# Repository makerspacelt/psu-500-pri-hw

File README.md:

This is atempt to design a 500W PSU primary side 

Dev NOTE: before commit, run `./kibot.sh` to regenerate documentation, gerbers and other assets.

* [schematics.pdf](gen/schematics.pdf)
* [pcb.pdf with dimensions](gen/pcb.pdf)

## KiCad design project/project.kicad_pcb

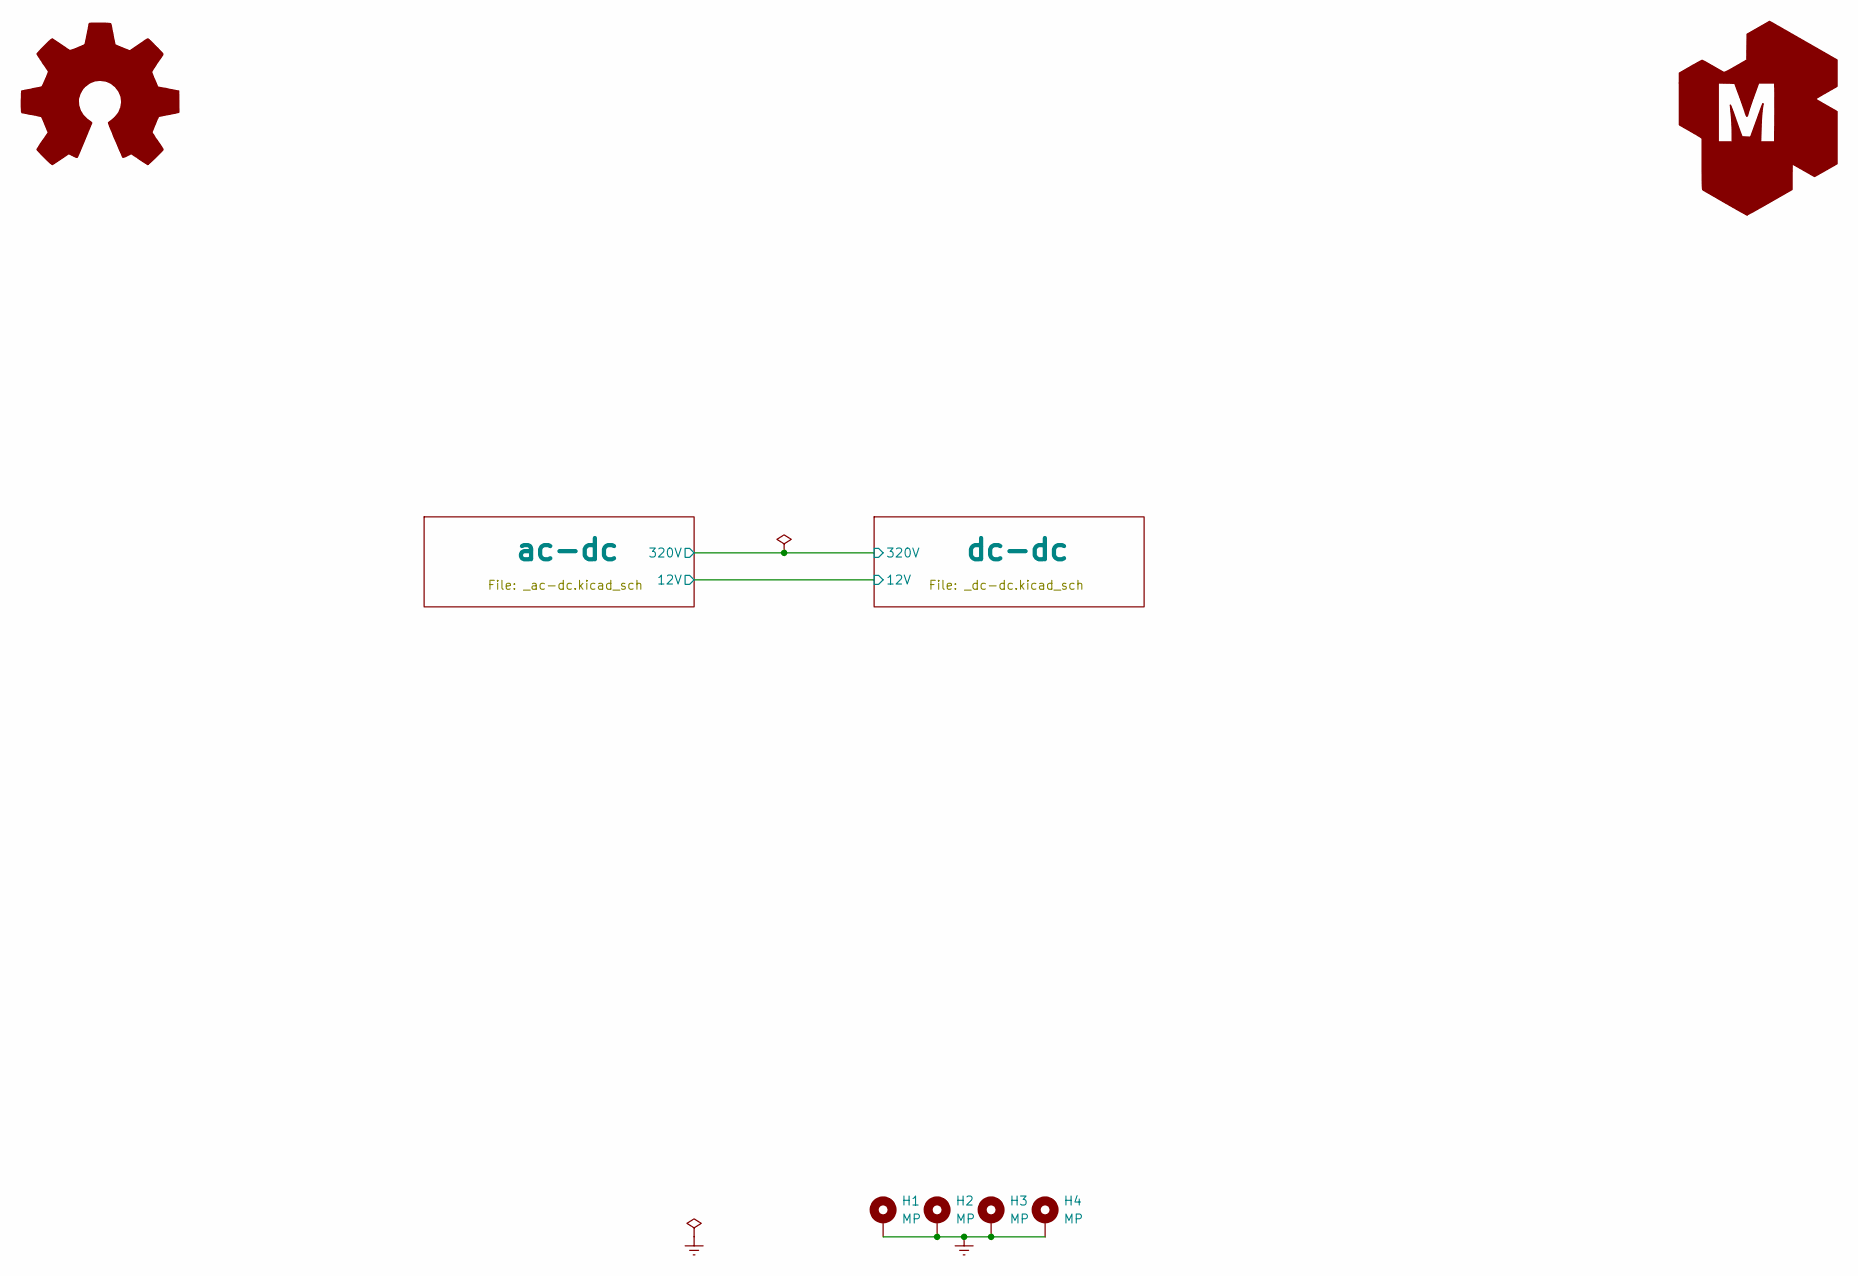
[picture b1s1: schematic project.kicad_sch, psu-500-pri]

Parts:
G1: Logo_Open_Hardware_Large; OSHW-Symbol_6.7x6mm_SilkScreen
G2: LOGO_KMS; logo_kms_small_silkscreen
H1, H2, H3, H4: MP; MountingHole_4.3mm_M4_Pad_Via

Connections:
Earth: H1.1, H2.1, H3.1, H4.1; also elsewhere on the board

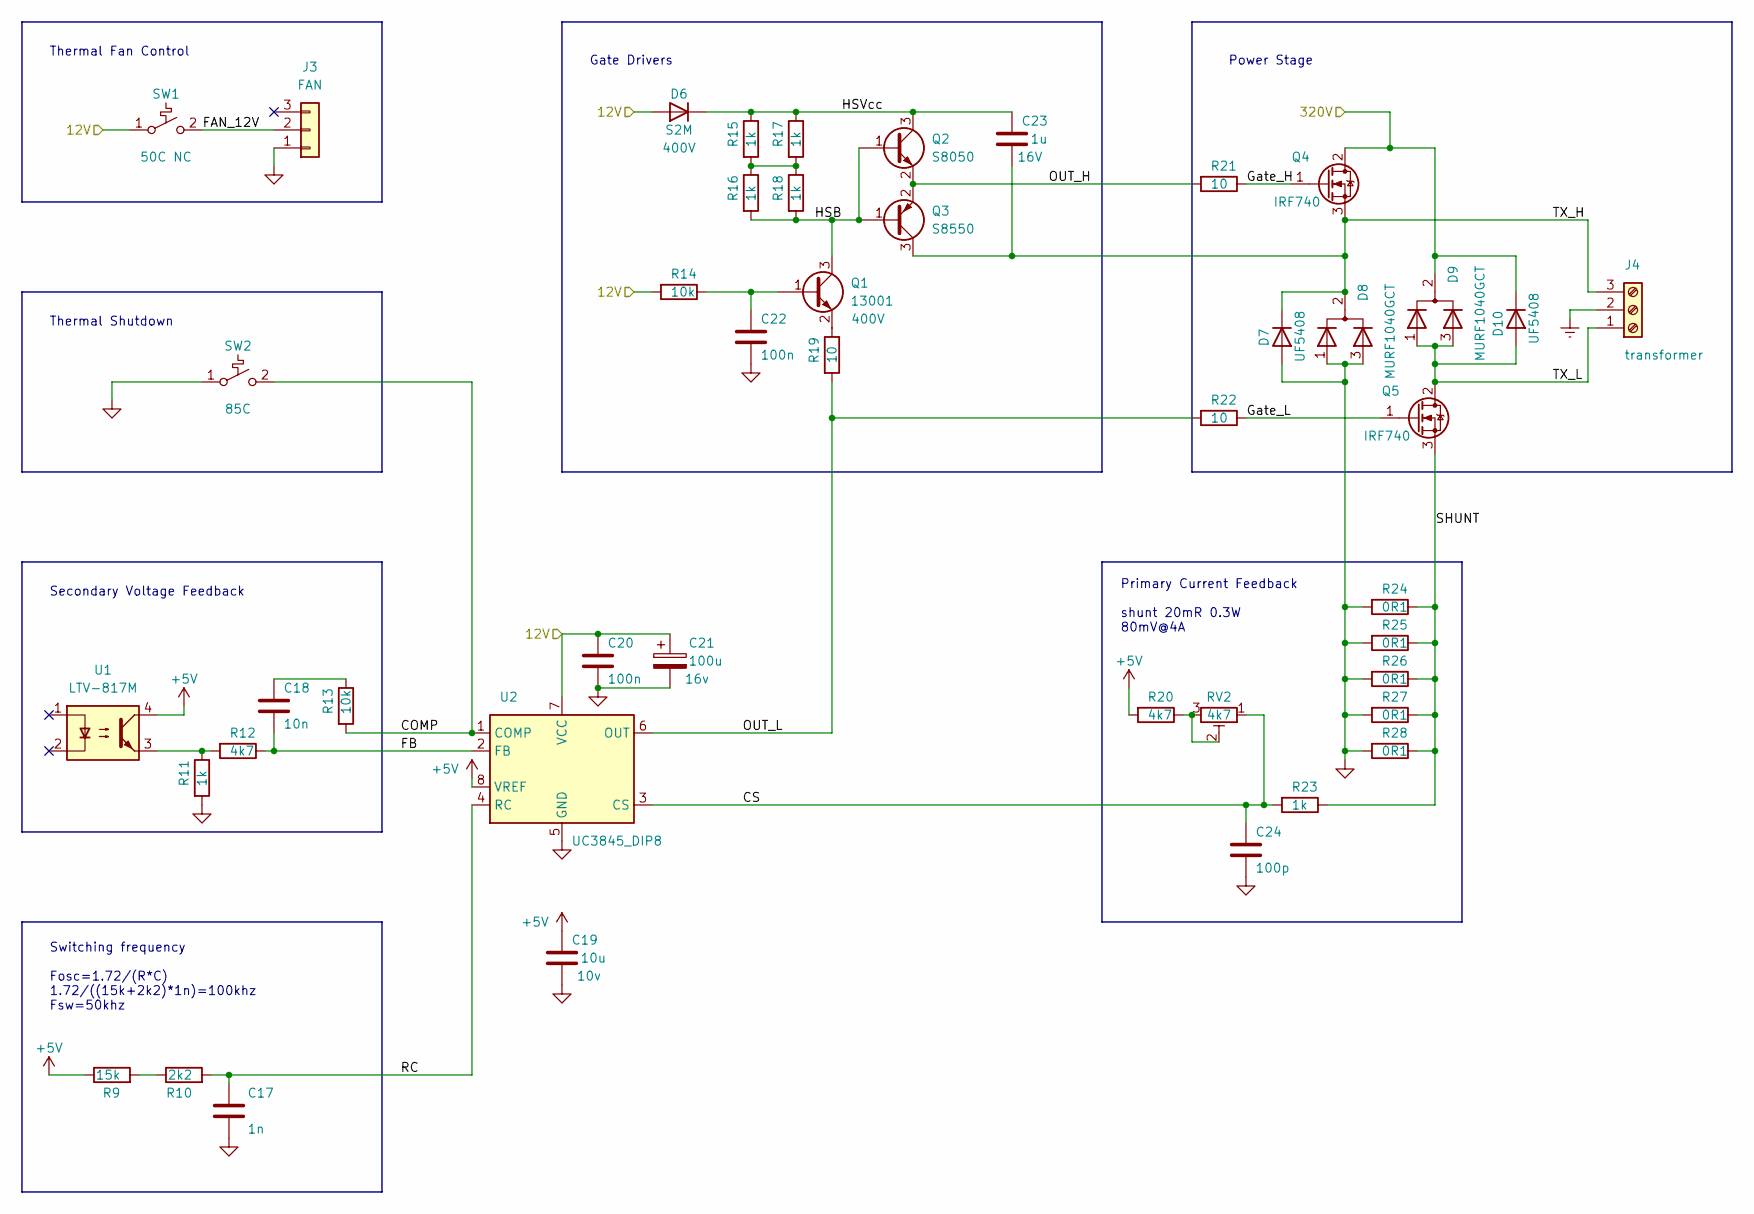
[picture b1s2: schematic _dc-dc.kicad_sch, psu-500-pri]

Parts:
C17: 1n; C_0805_2012Metric_Pad1.18x1.45mm_HandSolder
C18: 10n; C_0805_2012Metric_Pad1.18x1.45mm_HandSolder
C19: 10u; C_0805_2012Metric_Pad1.18x1.45mm_HandSolder
C20, C22: 100n; C_0805_2012Metric_Pad1.18x1.45mm_HandSolder
C21: 100u; CP_Elec_10x10
C23: 1u; C_0805_2012Metric_Pad1.18x1.45mm_HandSolder
C24: 100p; C_0805_2012Metric_Pad1.18x1.45mm_HandSolder
D6: S2M; D_SMA_Handsoldering
D7, D10: UF5408; D_DO-201AD_P15.24mm_Horizontal
D8, D9: MURF1040GCT; TO-220-3_Horizontal_TabUp; LCSC# C2995510
J3: FAN; Molex_KK-254_AE-6410-03A_1x03_P2.54mm_Vertical
J4: transformer; TerminalBlock_Phoenix_MKDS-1,5-3_1x03_P5.00mm_Horizontal
Q1: 13001; SOT-23; LCSC# C5261071
Q2: S8050; SOT-23
Q3: S8550; SOT-23
Q4, Q5: IRF740; TO-220-3_Horizontal_TabUp
R9: 15k; R_0805_2012Metric_Pad1.20x1.40mm_HandSolder
R10: 2k2; R_0805_2012Metric_Pad1.20x1.40mm_HandSolder
R11, R15, R16, R17, R18, R23: 1k; R_0805_2012Metric_Pad1.20x1.40mm_HandSolder
R12, R20: 4k7; R_0805_2012Metric_Pad1.20x1.40mm_HandSolder
R13, R14: 10k; R_0805_2012Metric_Pad1.20x1.40mm_HandSolder
R19, R21, R22: 10; R_0805_2012Metric_Pad1.20x1.40mm_HandSolder
R24, R25, R26, R27, R28: 0R1; R_0805_2012Metric_Pad1.20x1.40mm_HandSolder
RV2: 4k7; Potentiometer_Bourns_3296W_Vertical
SW1: 50C NC; TO-220-2_Horizontal_TabUp
SW2: 85C; TO-220-2_Horizontal_TabUp
U1: LTV-817M; DIP-4_W10.16mm; LCSC# C109226
U2: UC3845_DIP8; DIP-8_W7.62mm

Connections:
+5V: C19.1, R9.1, R20.2, U1.4, U2.8 (VREF)
/ac-dc/12V: C20.1, C21.1, D6.2 (A), R14.2, SW1.1 (A), U2.7 (VCC); also elsewhere on the board
/ac-dc/320V: D9.2 (A), D10.1 (K), Q4.2 (D); also elsewhere on the board
/dc-dc/COMP: R13.2, SW2.2 (B), U2.1 (COMP)
/dc-dc/CS: C24.1, R23.2, RV2.1, U2.3 (CS)
/dc-dc/FAN_12V: J3.2, SW1.2 (B)
/dc-dc/FB: C18.2, R12.1, U2.2 (FB)
/dc-dc/Gate_H: Q4.1 (G), R21.1
/dc-dc/Gate_L: Q5.1 (G), R22.1
/dc-dc/HSB: Q1.3 (C), Q2.1 (B), Q3.1 (B), R16.2, R18.2
/dc-dc/HSVcc: C23.1, D6.1 (K), Q2.3 (C), R15.1, R17.1
/dc-dc/OUT_H: Q2.2 (E), Q3.2 (E), R21.2
/dc-dc/OUT_L: R19.2, R22.2, U2.6 (OUT)
/dc-dc/RC: C17.1, R10.2, U2.4 (RC)
/dc-dc/SHUNT: Q5.3 (S), R23.1, R24.1, R25.1, R26.1, R27.1, R28.1
/dc-dc/TX_H: C23.2, D7.1 (K), D8.2 (A), J4.3, Q3.3 (C), Q4.3 (S)
/dc-dc/TX_L: D9.1 (K), D9.3 (K), D10.2 (A), J4.1, Q5.2 (D)
Earth: J4.2; also elsewhere on the board
GND: C17.2, C19.2, C20.2, C21.2, C22.2, C24.2, D7.2 (A), D8.1 (K), D8.3 (K), J3.1, R11.2, R24.2, R25.2, R26.2, R27.2, R28.2, SW2.1 (A), U2.5 (GND); also elsewhere on the board
unnamed: C18.1, R13.1
unnamed: C22.1, Q1.1 (B), R14.1
unnamed: Q1.2 (E), R19.1
unnamed: R9.2, R10.1
unnamed: R11.1, R12.2, U1.3
unnamed: R15.2, R16.1, R17.2, R18.1
unnamed: R20.1, RV2.2, RV2.3

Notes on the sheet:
Switching frequency Fosc=1.72/(R*C) 1.72/((15k+2k2)*1n)=100khz Fsw=50khz
Primary Current Feedback shunt 20mR 0.3W 80mV@4A
Gate Drivers
Thermal Fan Control
Thermal Shutdown
Secondary Voltage Feedback
Power Stage

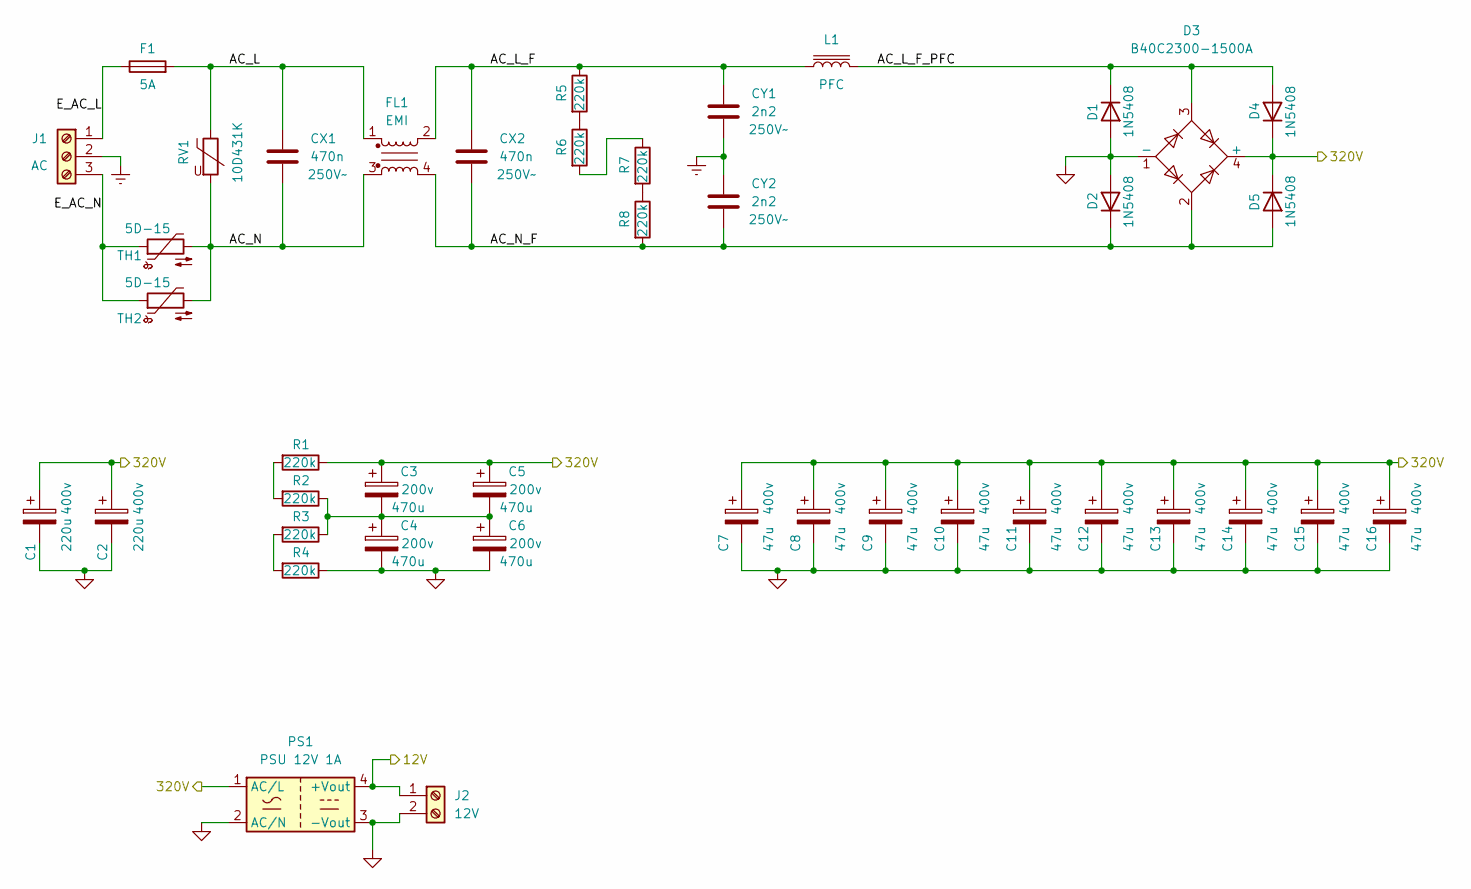
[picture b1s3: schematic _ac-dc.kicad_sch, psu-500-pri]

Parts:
C1, C2: 220u; CP_Radial_D30.0mm_P10.00mm_SnapIn
C3, C4, C5, C6: 470u; CP_Radial_D24.0mm_P10.00mm_SnapIn
C7, C8, C9, C10, C11, C12, C13, C14, C15, C16: 47u; CP_Radial_D16.0mm_P7.50mm
CX1, CX2: 470n; C_Rect_L19.0mm_W9.0mm_P15.00mm_MKS4
CY1, CY2: 2n2; C_Disc_D9.0mm_W5.0mm_P7.50mm
D1, D2, D4, D5: 1N5408; D_DO-201AD_P15.24mm_Horizontal
D3: B40C2300-1500A; Diode_Bridge_19.0x3.5x10.0mm_P5.0mm
F1: 5A; Fuseholder_Cylinder-5x20mm_Schurter_0031_8201_Horizontal_Op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
FL1: EMI; L_CommonMode_Toroid_Vertical_L34.3mm_W20.3mm_Px15.24mm_Py22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
J1: AC; TerminalBlock_Phoenix_MKDS-1,5-3_1x03_P5.00mm_Horizontal
J2: 12V; TerminalBlock_Phoenix_MKDS-1,5-2-5.08_1x02_P5.08mm_Horizont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
L1: PFC; JWT_A3963_1x02_P3.96mm_Vertical
PS1: PSU 12V 1A; Converter_ACDC_HiLink_HLK-PMxx
R1, R2, R3, R4, R5, R6, R7, R8: 220k; R_0805_2012Metric_Pad1.20x1.40mm_HandSolder
RV1: 10D431K; RV_Disc_D12mm_W5.4mm_P7.5mm; LCSC# C317794
TH1, TH2: 5D-15; C_Disc_D12.5mm_W5.0mm_P7.50mm

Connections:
/ac-dc/12V: J2.1, PS1.4 (+Vout); also elsewhere on the board
/ac-dc/320V: C1.1, C2.1, C3.1, C5.1, C7.1, C8.1, C9.1, C10.1, C11.1, C12.1, C13.1, C14.1, C15.1, C16.1, D3.4 (+), D4.1 (K), D5.1 (K), PS1.1 (AC/L), R1.1; also elsewhere on the board
/ac-dc/AC_L: CX1.1, F1.2, FL1.1, RV1.1
/ac-dc/AC_L_F: CX2.1, CY1.1, FL1.2, L1.1, R5.1
/ac-dc/AC_L_F_PFC: D1.1 (K), D3.3, D4.2 (A), L1.2
/ac-dc/AC_N: CX1.2, FL1.3, RV1.2, TH1.2, TH2.2
/ac-dc/AC_N_F: CX2.2, CY2.2, D2.1 (K), D3.2, D5.2 (A), FL1.4, R8.2
/ac-dc/E_AC_L: F1.1, J1.1
/ac-dc/E_AC_N: J1.3, TH1.1, TH2.1
Earth: CY1.2, CY2.1, J1.2; also elsewhere on the board
GND: C1.2, C2.2, C4.2, C6.2, C7.2, C8.2, C9.2, C10.2, C11.2, C12.2, C13.2, C14.2, C15.2, C16.2, D1.2 (A), D2.2 (A), D3.1 (-), J2.2, PS1.2 (AC/N), PS1.3 (-Vout), R4.1; also elsewhere on the board
unnamed: C3.2, C4.1, C5.2, C6.1, R2.1, R3.1
unnamed: R1.2, R2.2
unnamed: R3.2, R4.2
unnamed: R5.2, R6.1
unnamed: R6.2, R7.1
unnamed: R7.2, R8.1

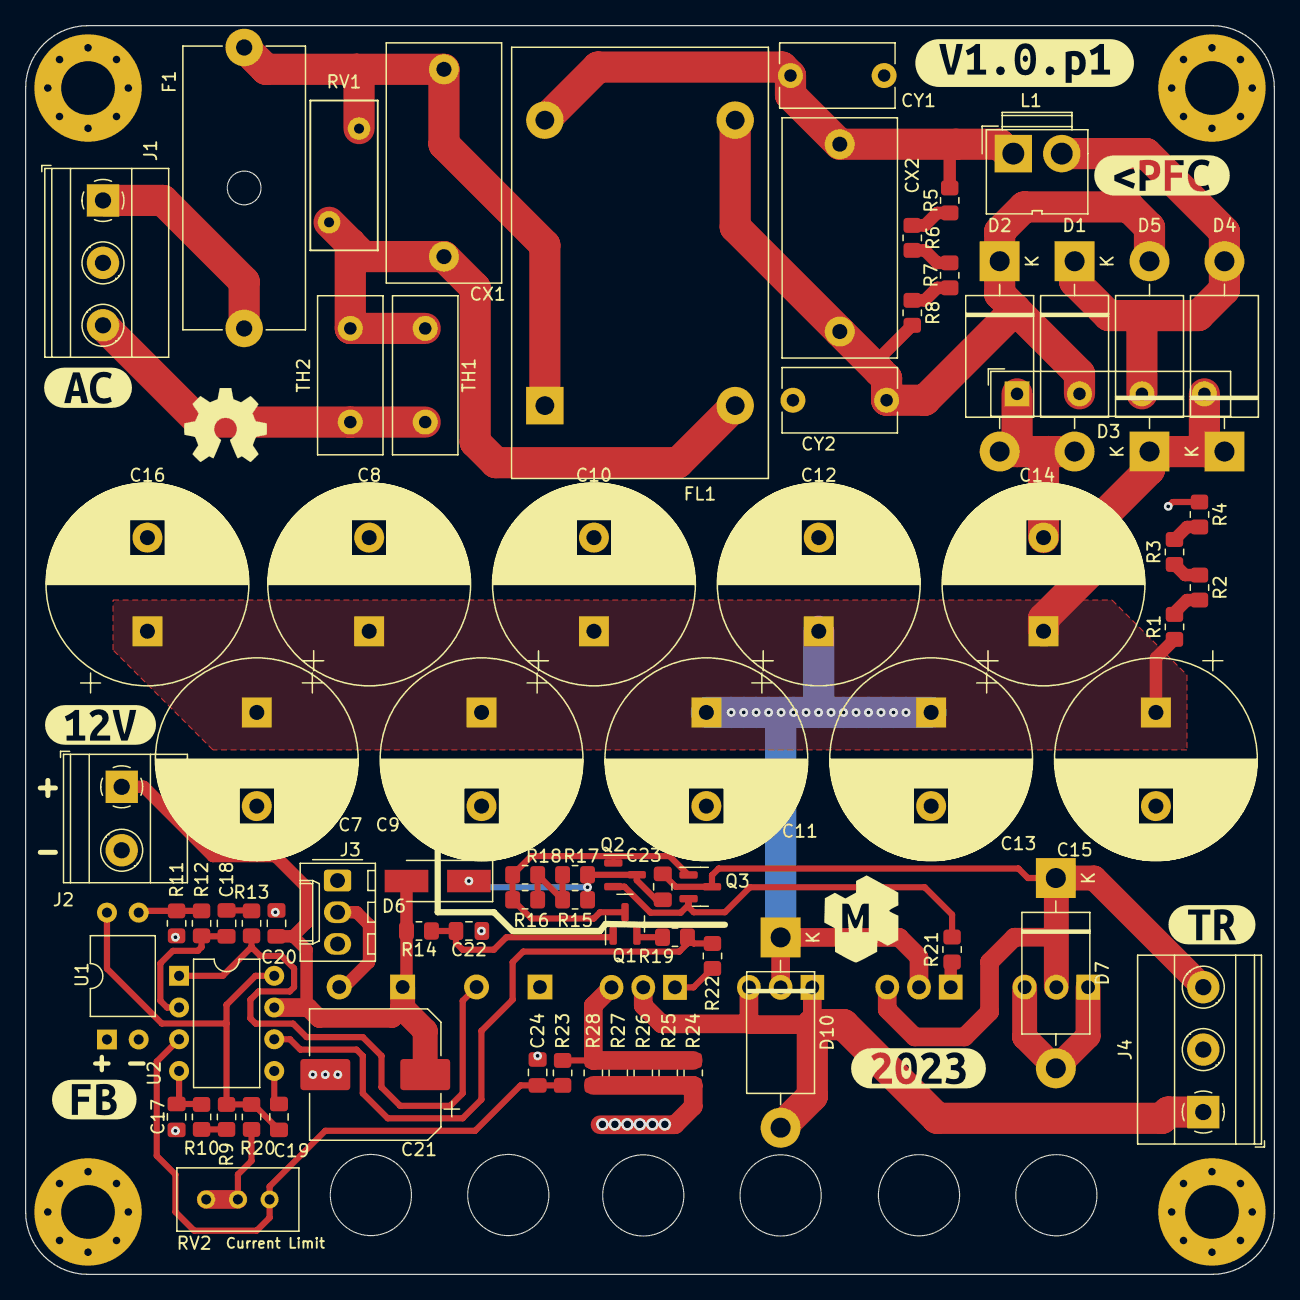
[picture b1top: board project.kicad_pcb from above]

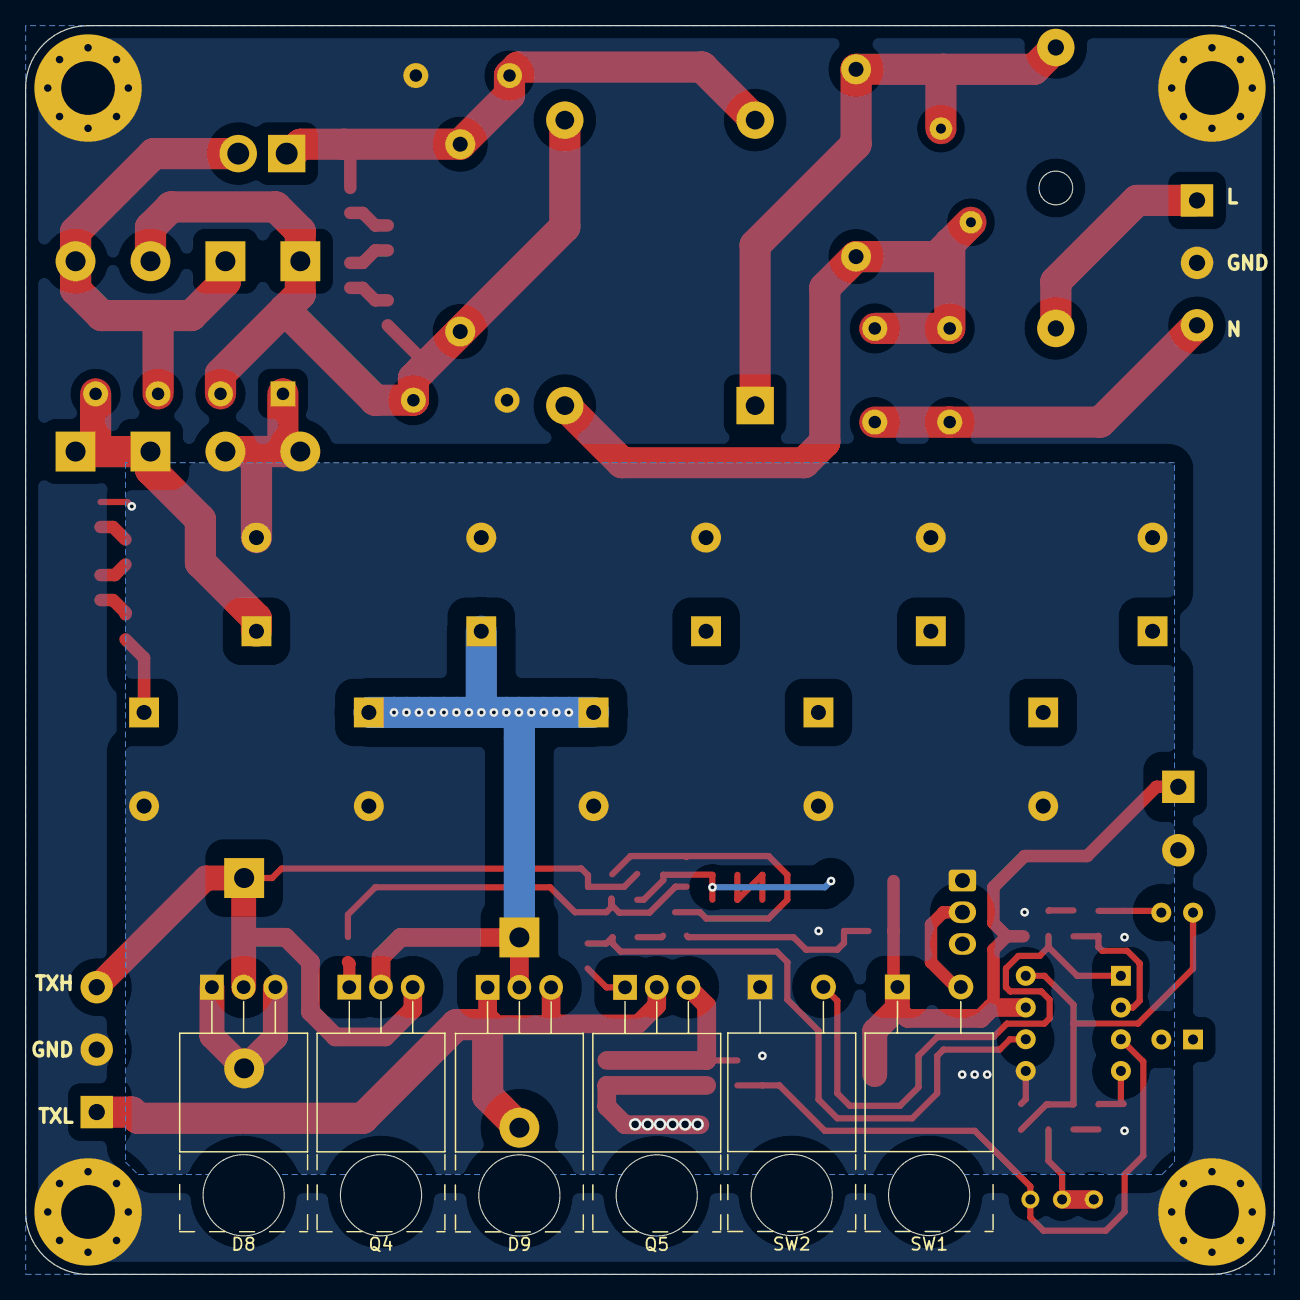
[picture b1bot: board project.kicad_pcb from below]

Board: 2 copper layers, 100.0 x 100.0 mm, 93 parts (6 on the bottom side), 39 nets.

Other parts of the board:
kibuzzard-64DA8E2C: G***; kibuzzard-64DA8E2C
kibuzzard-64DC9B3C: G***; kibuzzard-64DC9B3C
kibuzzard-64DC9B5D: G***; kibuzzard-64DC9B5D
kibuzzard-64DC9BC4: G***; kibuzzard-64DC9BC4
kibuzzard-64DC9C08: G***; kibuzzard-64DC9C08
kibuzzard-64DCA2D6: G***; kibuzzard-64DCA2D6
kibuzzard-64DCA30C: G***; kibuzzard-64DCA30C

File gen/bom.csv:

"Row","Description","Part","References","Value","Footprint","Quantity Per PCB","Status","Datasheet","jlc-part-type","LCSC#","Value2"
"1","Unpolarized capacitor","C","C24","100p","C_0805_2012Metric_Pad1.18x1.45mm_HandSolder","1"," ","~","","",""
"2","Unpolarized capacitor","C","C17","1n","C_0805_2012Metric_Pad1.18x1.45mm_HandSolder","1"," ","~","","",""
"3","Unpolarized capacitor","C","C18","10n","C_0805_2012Metric_Pad1.18x1.45mm_HandSolder","1"," ","~","","",""
"4","Unpolarized capacitor","C","C20,C22","100n","C_0805_2012Metric_Pad1.18x1.45mm_HandSolder","2"," ","~","","",""
"5","Unpolarized capacitor","C","C23","1u","C_0805_2012Metric_Pad1.18x1.45mm_HandSolder","1"," ","~","","","16V"
"6","Unpolarized capacitor","C","C19","10u","C_0805_2012Metric_Pad1.18x1.45mm_HandSolder","1"," ","~","","","10v"
"7","Polarized capacitor","C_Polarized","C7,C8,C9,C10,C11,C12,C13,C14,C15,C16","47u","CP_Radial_D16.0mm_P7.50mm","10"," ","~","","","400v"
"8","Polarized capacitor","C_Polarized","C21","100u","CP_Elec_10x10","1"," ","~","","","16v"
"9","Polarized capacitor","C_Polarized","C1,C2","220u","CP_Radial_D30.0mm_P10.00mm_SnapIn","2"," ","~","","","400v"
"10","Polarized capacitor","C_Polarized","C3,C4,C5,C6","470u","CP_Radial_D24.0mm_P10.00mm_SnapIn","4"," ","~","","","200v"
"11","Unpolarized capacitor","C","CX1,CX2","470n","C_Rect_L19.0mm_W9.0mm_P15.00mm_MKS4","2"," ","https://datasheet.lcsc.com/lcsc/C5454415.pdf","","C5454415","250V~"
"12","Unpolarized capacitor","C","CY1,CY2","2n2","C_Disc_D9.0mm_W5.0mm_P7.50mm","2"," ","https://datasheet.lcsc.com/lcsc/C5355118.pdf","","C5355118","250V~"
"13","Silicon Bridge Rectifier, 40V Vrms, 1.5A If, pins=-AA+, SIL-package","B40C2300-1500A","D3","GBU1010","Diode_Bridge_19.0x3.5x10.0mm_P5.0mm","1"," ","https://datasheet.lcsc.com/lcsc/2208121800_SEP-GBU1010_C5127096.pdf","","C5127096",""
"14","Dual diode, common anode on pin 1","D_Dual_CommonCathode_AKA_Parallel","D8,D9","MURF1040GCT","TO-220-3_Horizontal_TabUp","2"," ","https://datasheet.lcsc.com/lcsc/2205111516_DIYI-Elec-Tech-MU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","","C2995510",""
"15","1000V 3A Soft Recovery Ultrafast Rectifier Diode, DO-201AD","UF5408","D6","S2M","D_SMA_Handsoldering","1"," ","https://datasheet.lcsc.com/lcsc/1811101212_Shandong-Jingdao-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","","","400V"
"16","1000V 3A General Purpose Rectifier Diode, DO-201AD","1N5408","D7,D10","UF5408","D_DO-201AD_P15.24mm_Horizontal","2"," ","https://datasheet.lcsc.com/lcsc/1912111437_SUNMATE-Elec-UF54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","","",""
"17","1000V 3A General Purpose Rectifier Diode, DO-201AD","1N5408","D1,D2,D4,D5","~","D_DO-201AD_P15.24mm_Horizontal","4"," ","~","","",""
"18","Fuse","Fuse","F1","5A","Fuseholder_Cylinder-5x20mm_Schurter_0031_8201_Horizontal_Open","1"," ","https://datasheet.lcsc.com/lcsc/C717030.pdf","","C717030",""
"19","EMI 2-inductor common mode filter","Filter_EMI_CommonMode","FL1","EMI","L_CommonMode_Toroid_Vertical_L34.3mm_W20.3mm_Px15.24mm_Py22.86mm_Bourns_8100","1"," ","https://datasheet.lcsc.com/lcsc/2201121530_PROD-Tech-PDUUAT1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","","C2932158",""
"20","Generic screw terminal, single row, 01x02, script generated (kicad-library-utils/schlib/autogen/connector/)","Screw_Terminal_01x02","J2","12V","TerminalBlock_Phoenix_MKDS-1,5-2-5.08_1x02_P5.08mm_Horizontal","1"," ","~","","",""
"21","Generic screw terminal, single row, 01x03, script generated (kicad-library-utils/schlib/autogen/connector/)","Screw_Terminal_01x03","J1,J4","AC","TerminalBlock_Phoenix_MKDS-1,5-3_1x03_P5.00mm_Horizontal","2"," ","~","","",""
"22","Generic connector, single row, 01x03, script generated (kicad-library-utils/schlib/autogen/connector/)","Conn_01x03","J3","FAN","Molex_KK-254_AE-6410-03A_1x03_P2.54mm_Vertical","1"," ","~","","",""
"23","Inductor with iron core","L_Iron","L1","PFC","JWT_A3963_1x02_P3.96mm_Vertical","1"," ","~","","",""
"24","Compact AC/DC board mount power module 3W 5V","HLK-PM01","PS1","PSU 12V 1A","Converter_ACDC_HiLink_HLK-PMxx","1"," ","http://www.hlktech.net/product_detail.php?ProId=54","","",""
"25","NPN transistor, base/emitter/collector","Q_NPN_BEC","Q1","13001","SOT-23","1"," ","https://datasheet.lcsc.com/lcsc/2212161630_HXY-MOSFET-13001_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","","C5261071","400V"
"26","10A Id, 400V Vds, N-Channel Power MOSFET, 500mOhm Rds, TO-220AB","IRF740","Q4,Q5","IRF740","TO-220-3_Horizontal_TabUp","2"," ","https://datasheet.lcsc.com/lcsc/2203231030_Minos-IRF740_C298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","","C2980280",""
"27","NPN transistor, base/emitter/collector","Q_NPN_BEC","Q2","S8050","SOT-23","1"," ","https://datasheet.lcsc.com/lcsc/2304140030_Jiangsu-Changjing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","","",""
"28","PNP transistor, base/emitter/collector","Q_PNP_BEC","Q3","S8550","SOT-23","1"," ","https://datasheet.lcsc.com/lcsc/2205061000_Guangdong-Hottech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","","",""
"29","Resistor","R","R24,R25,R26,R27,R28","0R1","R_0805_2012Metric_Pad1.20x1.40mm_HandSolder","5"," ","~","","",""
"30","Resistor","R","R19,R21,R22","10","R_0805_2012Metric_Pad1.20x1.40mm_HandSolder","3"," ","~","","",""
"31","Resistor","R","R11,R15,R16,R17,R18,R23","1k","R_0805_2012Metric_Pad1.20x1.40mm_HandSolder","6"," ","~","","",""
"32","Resistor","R","R10","2k2","R_0805_2012Metric_Pad1.20x1.40mm_HandSolder","1"," ","~","","",""
"33","Resistor","R","R12,R20","4k7","R_0805_2012Metric_Pad1.20x1.40mm_HandSolder","2"," ","~","","",""
"34","Resistor","R","R13,R14","10k","R_0805_2012Metric_Pad1.20x1.40mm_HandSolder","2"," ","~","","",""
"35","Resistor","R","R9","15k","R_0805_2012Metric_Pad1.20x1.40mm_HandSolder","1"," ","~","","",""
"36","Resistor","R","R1,R2,R3,R4,R5,R6,R7,R8","220k","R_0805_2012Metric_Pad1.20x1.40mm_HandSolder","8"," ","~","","",""
"37","Trim-potentiometer","R_Potentiometer_Trim","RV2","4k7","Potentiometer_Bourns_3296W_Vertical","1"," ","~","","",""
"38","Voltage dependent resistor","Varistor","RV1","10D431K","RV_Disc_D12mm_W5.4mm_P7.5mm","1"," ","https://datasheet.lcsc.com/lcsc/2304140030_COV-10D431K_C317794.pdf","","C317794",""
"39","Single Pole Single Throw (SPST) switch, temperature dependent","SW_SPST_Temperature","SW1","50C NC","TO-220-2_Horizontal_TabUp","1"," ","~","","",""
"40","Single Pole Single Throw (SPST) switch, temperature dependent","SW_SPST_Temperature","SW2","85C","TO-220-2_Horizontal_TabUp","1"," ","~","","",""
"41","Flash symbol, small","SYM_Flash_Small","SYM1","SYM_Flash_Small","qr","1"," ","~","","",""
"42","Temperature dependent resistor, negative temperature coefficient","Thermistor_NTC","TH1,TH2","5D-15","C_Disc_D12.5mm_W5.0mm_P7.50mm","2"," ","https://datasheet.lcsc.com/lcsc/C2839620.pdf","","C2839620",""
"43","DC Optocoupler, Vce 35V, CTR 50%, DIP-4","LTV-817M","U1","LTV-817M","DIP-4_W10.16mm","1"," ","http://www.us.liteon.com/downloads/LTV-817-827-847.PDF","","C109226",""
"44","Current-Mode PWM Controllers, 50% Duty Cycle, 8.4V/7.6V UVLO, PDIP-8","UC3845_DIP8","U2","UC3845B","DIP-8_W7.62mm","1"," ","https://datasheet.lcsc.com/lcsc/2007031829_UMW-Youtai-Semico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","","C347460",""

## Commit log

2023-06-12 adding CERN license
2023-06-12 Add files via upload
    Kicad schematic files
2023-08-12 starting from square one
2023-08-12 adding more things and specifying components
2023-08-14 starting pcb
2023-08-16 finishing pcb
2023-08-16 small power traces rearrangement
2023-08-18 finalizing pcb and adding gerbers
2023-08-18 adding few part numbers to the bom
